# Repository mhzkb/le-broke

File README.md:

silly wacky split-but-not-split adaptation of le chiffre.

mx and choc v1 support
2u or 2x 1u bottom row support

ez to assemble, reversible pcb, face down n!n/pro micro (zmk only!!), requires diodes and 2 6x6 buttons.

WATCH YOUR DIODE ORIENTATION!!! IT MATTERS!

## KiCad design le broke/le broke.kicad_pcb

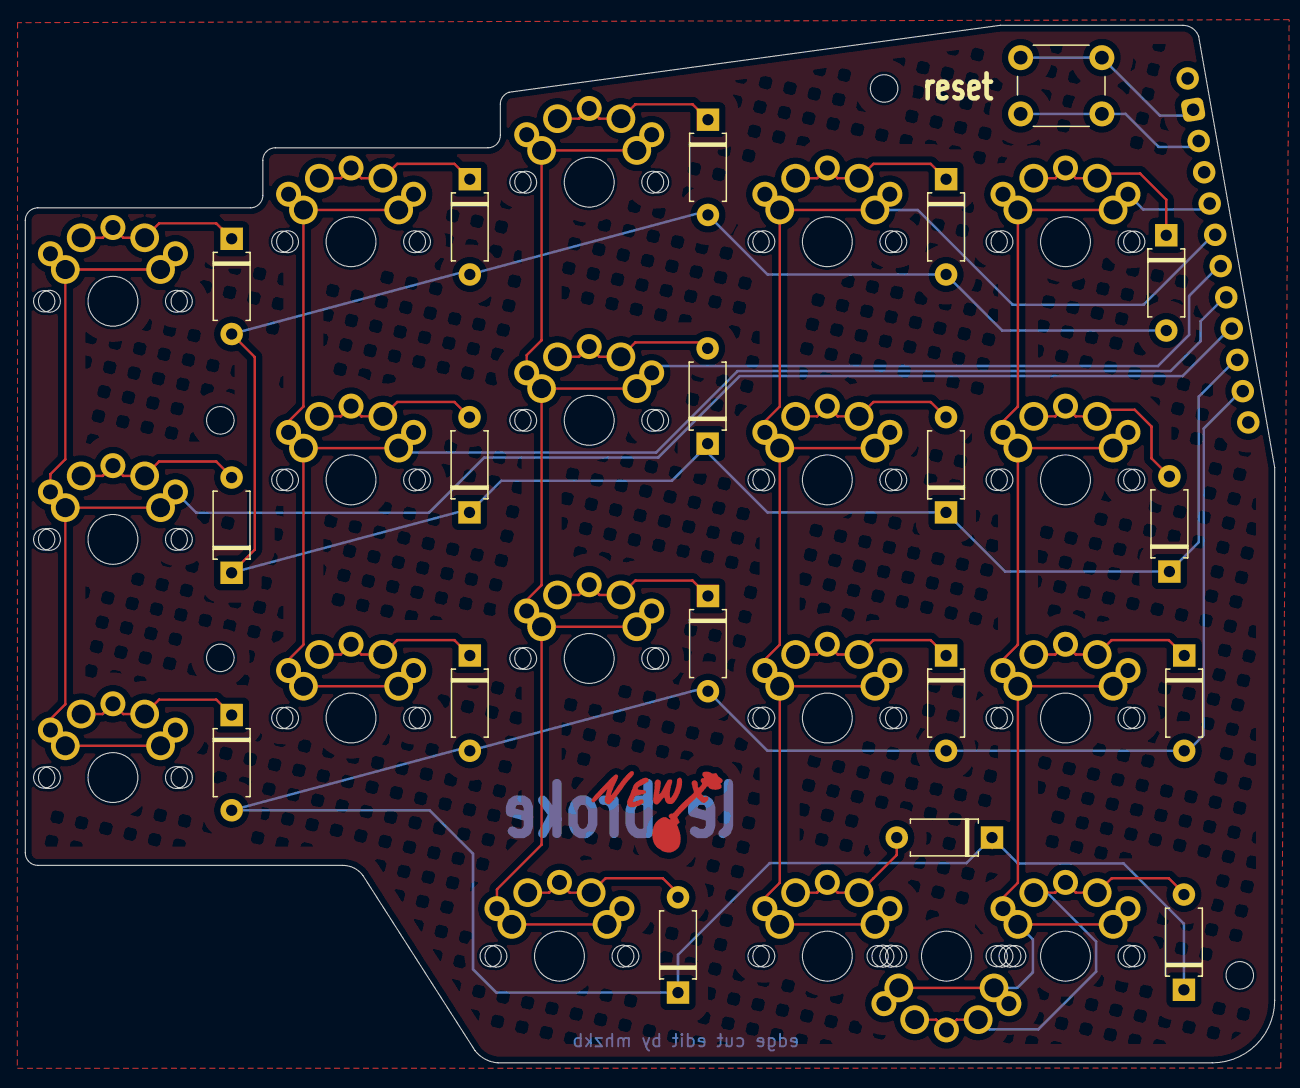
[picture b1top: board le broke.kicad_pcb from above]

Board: 2 copper layers, 99.9 x 83.0 mm, 39 parts (1 on the bottom side), 27 nets.

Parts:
D1, D2, D3, D4, D5, D6, D7, D8, D9, D10, D11, D12, D13, D14, D15, D16, D17, D18: D_Small; D_A-405_P7.62mm_Horizontal
MX1, MX2, MX3, MX4, MX5, MX6, MX7, MX8, MX9, MX10, MX11, MX12, MX13, MX14, MX15, MX16, MX17, MX18, MX18#2: MX_SW_solder; SW_MX_1u_rev
SW1: SW_Push; SW_PUSH_6mm
U1: ProMicro; ProMicro_Reversible_Single

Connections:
COL0: MX5.1, MX10.1, MX15.1, U1.21 (B1)
COL1: MX2.1, MX7.1, MX12.1, U1.20 (F7)
COL2: MX1.1, MX6.1, MX11.1, MX16.1, U1.19 (F6)
COL3: MX3.1, MX8.1, MX13.1, MX17.1, U1.18 (F5)
COL4: MX4.1, MX9.1, MX14.1, MX18#2.1, U1.17 (F4)
unnamed: D1.1 (K), MX1.2
unnamed: D2.1 (K), MX2.2
unnamed: D3.1 (K), MX3.2
unnamed: D4.1 (K), MX4.2
unnamed: D5.1 (K), MX5.2
unnamed: D6.2 (A), MX6.2
unnamed: D7.2 (A), MX7.2
unnamed: D8.2 (A), MX8.2
unnamed: D9.2 (A), MX9.2
unnamed: D10.2 (A), MX10.2
unnamed: D11.1 (K), MX11.2
unnamed: D12.1 (K), MX12.2
unnamed: D13.1 (K), MX13.2
unnamed: D14.1 (K), MX14.2
unnamed: D15.1 (K), MX15.2
unnamed: D16.2 (A), MX16.2
unnamed: D17.2 (A), MX17.2
unnamed: D18.2 (A), MX18#2.2
unnamed: SW1.1, U1.14 (GND)
unnamed: SW1.2, U1.15 (RST)
ROW0: D1.2 (A), D2.2 (A), D3.2 (A), D4.2 (A), D5.2 (A), D6.1 (K), D7.1 (K), D8.1 (K), D9.1 (K), D10.1 (K), U1.22 (B3)
ROW1: D11.2 (A), D12.2 (A), D13.2 (A), D14.2 (A), D15.2 (A), D16.1 (K), D17.1 (K), D18.1 (K), U1.23 (B2)

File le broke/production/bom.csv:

Designator,Footprint,Quantity,Value,LCSC Part #
"D1, D10, D11, D12, D13, D14, D15, D16, D17, D18, D2, D3, D4, D5, D6, D7, D8, D9",D_A-405_P7.62mm_Horizontal,18,D_Small,
"MX1, MX10, MX11, MX12, MX13, MX14, MX15, MX16, MX17, MX18_2, MX18, MX2, MX3, MX4, MX5, MX6, MX7, MX8, MX9",choc_mx_rev,19,MX_SW_solder,
SW1,SW_PUSH_6mm,1,SW_Push,

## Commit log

2025-06-03 added kicad project
2025-06-03 worked
    routing cucked gotta fix
2025-06-04 did a lebroke thing idk
2025-06-04 added case DXFs fixed pcb
2025-06-05 added lebroke(?)
2025-06-11 added 3dp case files
2025-06-11 renamed cut case files
2025-06-26 added firmware
2025-06-26 epic style
2025-06-26 added images
2025-07-05 added 2u spacebar support
2025-07-05 added case files for v2
2025-07-09 updated default keymap
2025-07-09 added default keymap image
2025-07-09 added images, updated pcb image
2025-07-09 added STEP of assembled lebroke
2025-07-09 added edge cuts
2025-07-10 removed accidental lock file LOL
2025-07-22 added untested chocV2 pcb and gerbers
2025-08-28 Updated kicad folder
